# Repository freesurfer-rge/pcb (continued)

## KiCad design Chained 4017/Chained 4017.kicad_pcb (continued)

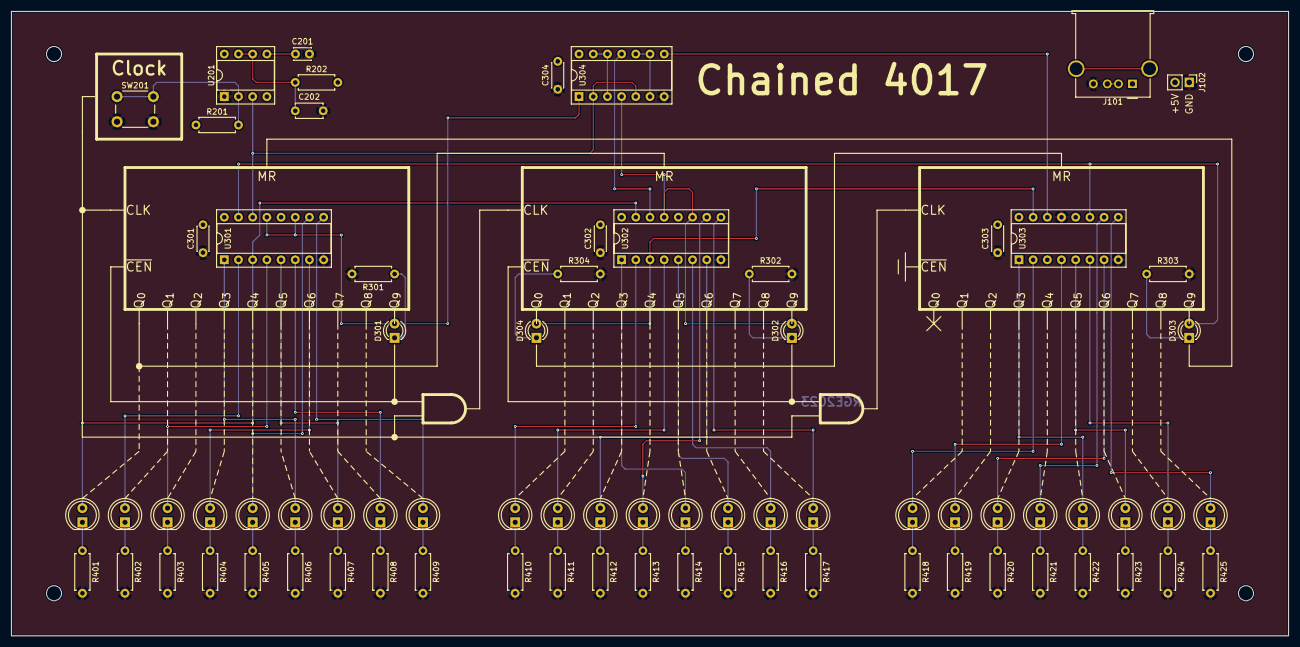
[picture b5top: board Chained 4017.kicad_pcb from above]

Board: 2 copper layers, 228.6 x 111.8 mm, 78 parts (0 on the bottom side), 69 nets.

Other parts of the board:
C301, C302, C303, C304: 0.1u; C_Disc_D4.3mm_W1.9mm_P5.00mm

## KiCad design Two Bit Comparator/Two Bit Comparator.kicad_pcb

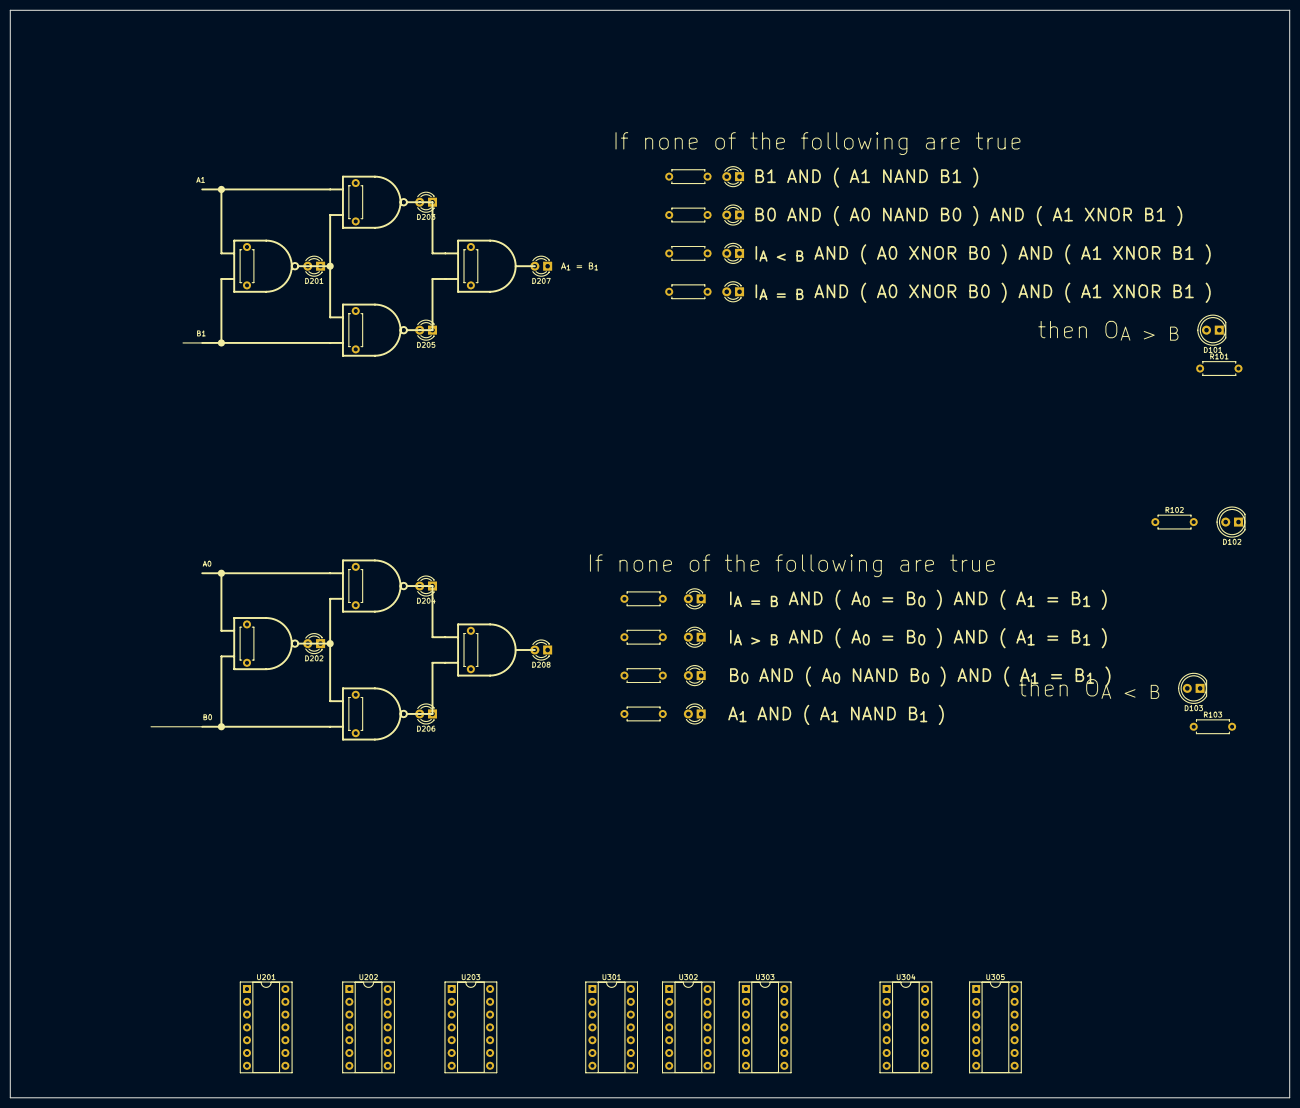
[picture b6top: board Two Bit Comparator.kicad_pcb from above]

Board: 2 copper layers, 254.0 x 215.9 mm, 46 parts (0 on the bottom side), 52 nets, no tracks yet.

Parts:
D101, D102, D103: LED; LED_D5.0mm
D201, D202, D203, D204, D205, D206, D207, D208, D301, D302, D303, D304, D305, D306, D307, D308: LED; LED_D3.0mm
R101, R102, R103, R201, R202, R203, R204, R205, R206, R207, R208, R301, R302, R303, R304, R305, R306, R307, R308: R; R_Axial_DIN0207_L6.3mm_D2.5mm_P7.62mm_Horizontal
U201, U202, U203: 74HC00; DIP-14_W7.62mm_Socket
U301, U302, U303: 74HC10; DIP-14_W7.62mm_Socket
U304, U305: 74HC08; DIP-14_W7.62mm_Socket

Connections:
+5V: U201.14 (VCC), U202.14 (VCC), U203.14 (VCC), U301.5, U301.13, U301.14 (VCC), U302.14 (VCC), U303.14 (VCC), U304.14 (VCC), U305.14 (VCC)
/Accumulate and Output/A0: U201.1, U202.4, U303.11
/Accumulate and Output/A1: U201.4, U202.1, U301.4
/Accumulate and Output/A_{0}NANDB_{0}: R202.1, U201.3, U202.5, U202.9, U302.2, U303.10
/Accumulate and Output/A_{0}XNORB_{0}: R208.1, U203.8, U302.4, U302.10, U303.2, U303.5, U305.12
/Accumulate and Output/A_{1}NANDB_{1}: R201.1, U201.6, U202.2, U202.12, U301.2, U301.3
/Accumulate and Output/A_{1}XNORB_{1}: R207.1, U203.11, U302.3, U302.9, U302.13, U303.1, U303.4, U303.9, U305.13
/Accumulate and Output/B0: U201.2, U202.10, U302.1
/Accumulate and Output/B1: U201.5, U202.13, U301.1
/Accumulate and Output/I_{A=B}: U302.11, U303.13, U304.13
/Accumulate and Output/O_{A<B}: R103.1, U305.8
/Accumulate and Output/O_{A=B}: R102.1, U304.11
/Accumulate and Output/O_{A>B}: R101.1, U304.8
/Accumulate and Output/c0: R301.1, U301.12, U304.1
/Accumulate and Output/c1: R302.1, U302.12, U304.2
/Accumulate and Output/c2: R303.1, U302.6, U304.4
/Accumulate and Output/c3: R304.1, U302.8, U304.5
/Accumulate and Output/c4: R305.1, U303.12, U305.1
/Accumulate and Output/c5: R306.1, U303.6, U305.2
/Accumulate and Output/c6: R307.1, U303.8, U305.4
/Accumulate and Output/c7: R308.1, U301.6, U305.5
/Compare/Ind0: R203.1, U202.3, U203.1
/Compare/Ind1: R205.1, U202.11, U203.2
/Compare/Ind3: R204.1, U202.6, U203.4
/Compare/Ind4: R206.1, U202.8, U203.5
GND: D101.1 (K), D102.1 (K), D103.1 (K), D201.1 (K), D202.1 (K), D203.1 (K), D204.1 (K), D205.1 (K), D206.1 (K), D207.1 (K), D208.1 (K), D301.1 (K), D302.1 (K), D303.1 (K), D304.1 (K), D305.1 (K), D306.1 (K), D307.1 (K), D308.1 (K), U201.7 (GND), U201.9, U201.10, U201.12, U201.13, U202.7 (GND), U203.7 (GND), U301.7 (GND), U301.9, U301.10, U301.11, U302.7 (GND), U303.7 (GND), U304.7 (GND), U305.7 (GND)
unnamed: D101.2 (A), R101.2
unnamed: D102.2 (A), R102.2
unnamed: D103.2 (A), R103.2
unnamed: D201.2 (A), R201.2
unnamed: D202.2 (A), R202.2
unnamed: D203.2 (A), R203.2
unnamed: D204.2 (A), R204.2
unnamed: D205.2 (A), R205.2
unnamed: D206.2 (A), R206.2
unnamed: D207.2 (A), R207.2
unnamed: D208.2 (A), R208.2
unnamed: D301.2 (A), R301.2
unnamed: D302.2 (A), R302.2
unnamed: D303.2 (A), R303.2
unnamed: D304.2 (A), R304.2
unnamed: D305.2 (A), R305.2
unnamed: D306.2 (A), R306.2
unnamed: D307.2 (A), R307.2
unnamed: D308.2 (A), R308.2
unnamed: U203.6, U203.9, U203.10
unnamed: U203.3, U203.12, U203.13
unnamed: U304.3, U304.9
unnamed: U304.6, U304.10
unnamed: U304.12, U305.11
unnamed: U305.3, U305.9
unnamed: U305.6, U305.10

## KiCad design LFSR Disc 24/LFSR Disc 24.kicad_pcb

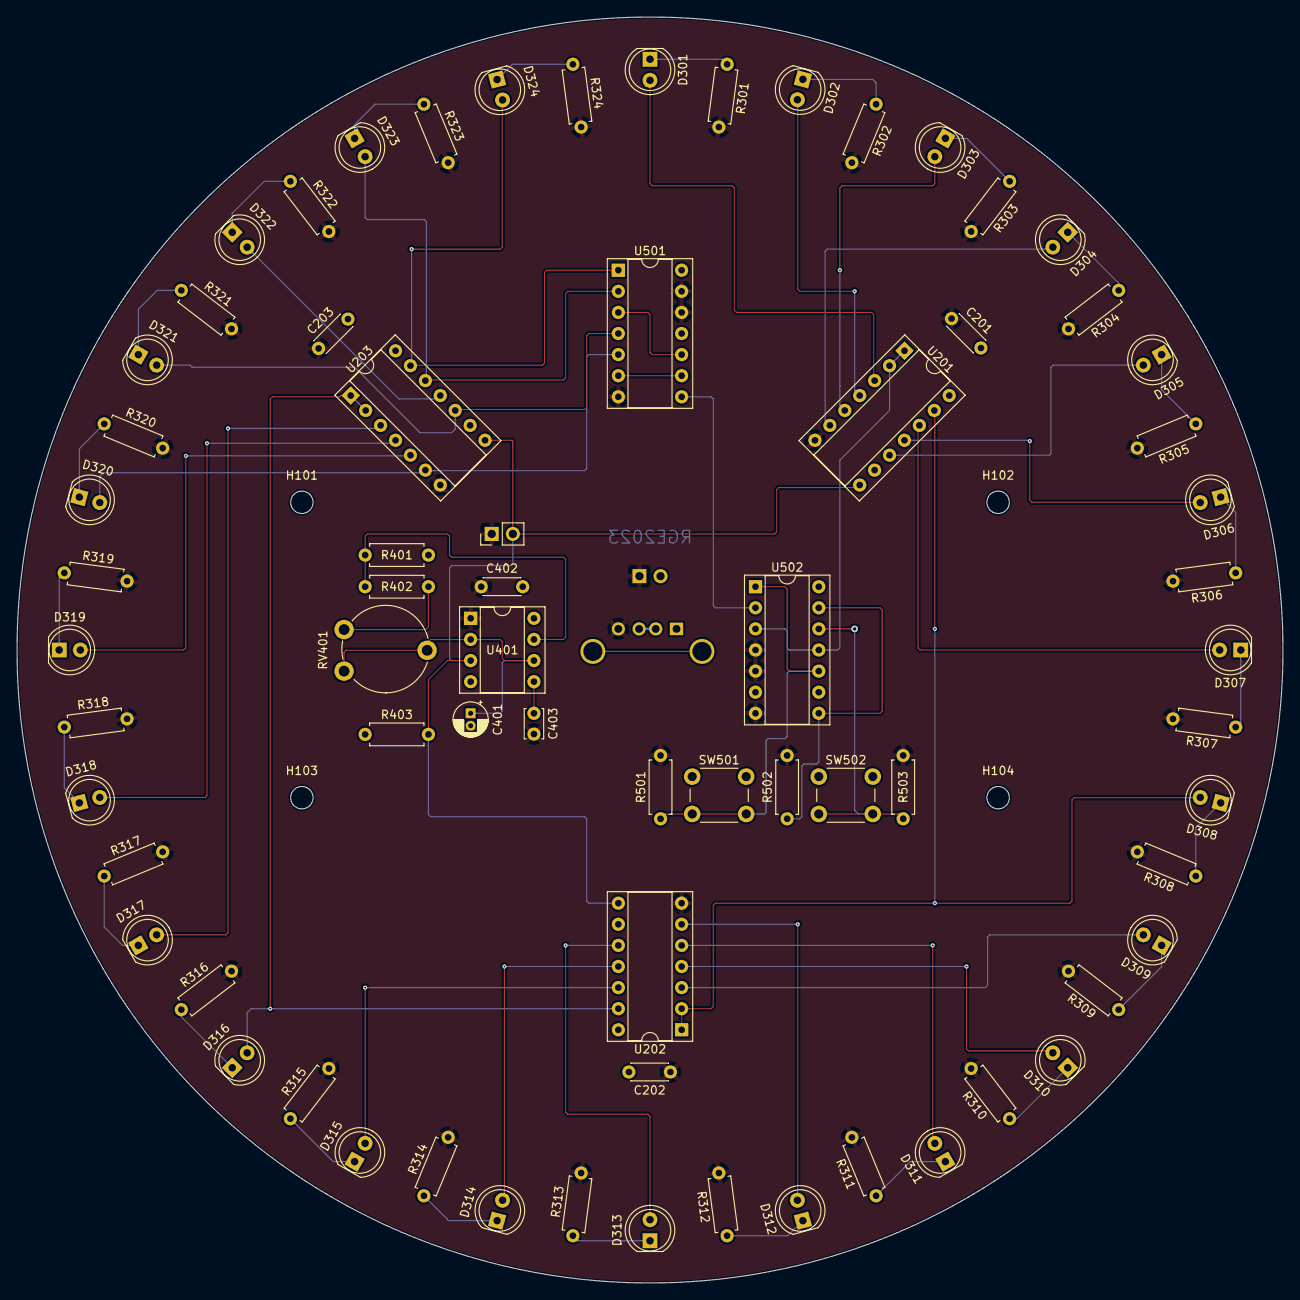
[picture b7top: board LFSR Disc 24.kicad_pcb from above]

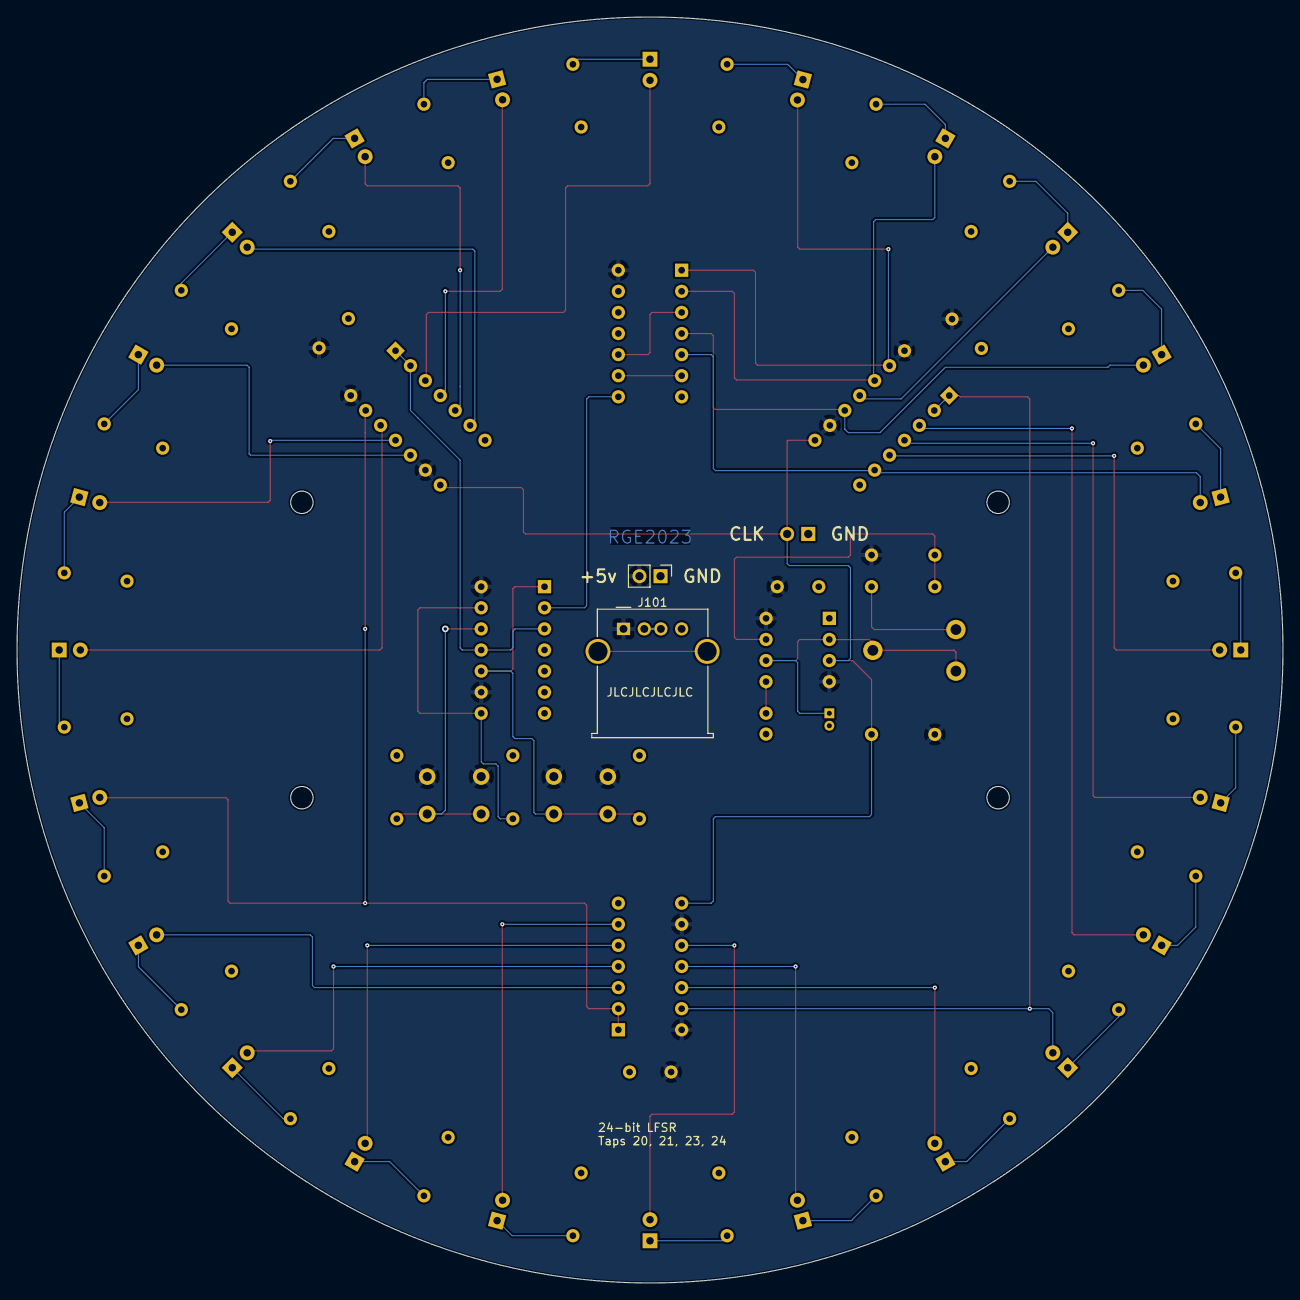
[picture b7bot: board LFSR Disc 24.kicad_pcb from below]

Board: 2 copper layers, 152.4 x 152.4 mm, 76 parts (2 on the bottom side), 63 nets.

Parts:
C201, C202, C203, C402: 0.1u; C_Disc_D4.3mm_W1.9mm_P5.00mm
C401: 10u; CP_Radial_D4.0mm_P1.50mm
C403: 0.01u; C_Disc_D3.4mm_W2.1mm_P2.50mm
D301, D302, D303, D304, D305, D306, D307, D308, D309, D310, D311, D312, D313, D314, D315, D316, D317, D318, D319, D320, D321, D322, D323, D324: LED; LED_D5.0mm
H101, H102, H103, H104: MountingHole; MountingHole_2.7mm_M2.5_ISO7380
J101: USB_A; USB_A_Molex_67643_Horizontal
J102, J401: Conn_01x02_Pin; PinHeader_1x02_P2.54mm_Vertical
R301, R302, R303, R304, R305, R306, R307, R308, R309, R310, R311, R312, R313, R314, R315, R316, R317, R318, R319, R320, R321, R322, R323, R324: 4k7; R_Axial_DIN0207_L6.3mm_D2.5mm_P7.62mm_Horizontal
R401: 10k; R_Axial_DIN0207_L6.3mm_D2.5mm_P7.62mm_Horizontal
R402: 2k2; R_Axial_DIN0207_L6.3mm_D2.5mm_P7.62mm_Horizontal
R403: 1k; R_Axial_DIN0207_L6.3mm_D2.5mm_P7.62mm_Horizontal
R501, R502, R503: 100k; R_Axial_DIN0207_L6.3mm_D2.5mm_P7.62mm_Horizontal
RV401: 100k; Potentiometer_Piher_PT-10-V10_Vertical
SW501, SW502: SW_SPST; SW_PUSH_6mm
U201, U202, U203: 74HC164; DIP-14_W7.62mm_Socket
U401: LM555xN; DIP-8_W7.62mm_Socket
U501: 74HC86; DIP-14_W7.62mm_Socket
U502: 74HCT125; DIP-14_W7.62mm_Socket

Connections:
+5V: C201.2, C202.2, C203.2, C402.2, J101.1 (VBUS), J102.2, R401.2, R403.1, SW501.1 (A), SW502.1 (A), U201.9 (~MR), U201.14 (VCC), U202.9 (~MR), U202.14 (VCC), U203.9 (~MR), U203.14 (VCC), U401.4 (R), U401.8 (VCC), U501.14 (VCC), U502.9, U502.14 (VCC)
/LED Output/LED1: D301.2 (A), U201.3 (Q0)
/LED Output/LED2: D302.2 (A), U201.4 (Q1)
/LED Output/LED3: D303.2 (A), U201.5 (Q2)
/LED Output/LED4: D304.2 (A), U201.6 (Q3)
/LED Output/LED5: D305.2 (A), U201.10 (Q4)
/LED Output/LED6: D306.2 (A), U201.11 (Q5)
/LED Output/LED7: D307.2 (A), U201.12 (Q6)
/LED Output/LED8: D308.2 (A), U201.13 (Q7), U202.1 (DSA), U202.2 (DSB)
/LED Output/LED9: D309.2 (A), U202.3 (Q0)
/LED Output/LED10: D310.2 (A), U202.4 (Q1)
/LED Output/LED11: D311.2 (A), U202.5 (Q2)
/LED Output/LED12: D312.2 (A), U202.6 (Q3)
/LED Output/LED13: D313.2 (A), U202.10 (Q4)
/LED Output/LED14: D314.2 (A), U202.11 (Q5)
/LED Output/LED15: D315.2 (A), U202.12 (Q6)
/LED Output/LED16: D316.2 (A), U202.13 (Q7), U203.1 (DSA), U203.2 (DSB)
/LED Output/LED17: D317.2 (A), U203.3 (Q0)
/LED Output/LED18: D318.2 (A), U203.4 (Q1)
/LED Output/LED19: D319.2 (A), U203.5 (Q2)
/LED Output/LED20: D320.2 (A), U203.6 (Q3), U501.5
/LED Output/LED21: D321.2 (A), U203.10 (Q4), U501.4
/LED Output/LED22: D322.2 (A), U203.11 (Q5)
/LED Output/LED23: D323.2 (A), U203.12 (Q6), U501.2
/LED Output/LED24: D324.2 (A), U203.13 (Q7), U501.1
/Shift Clock/CLK: J401.2, R403.2, U201.8 (CP), U202.8 (CP), U203.8 (CP), U401.3 (Q)
/Shift Clock/DIVIDER: R401.1, R402.1, U401.7 (DIS)
/Shift Clock/TRTHR: C401.1, RV401.1, RV401.2, U401.2 (TR), U401.6 (THR)
/Shift Registers/Feedback/NXTBIT: U201.1 (DSA), U201.2 (DSB), U502.3, U502.11
/Shift Registers/Feedback/~FEEDBACK: R501.1, SW501.2 (B), U502.1, U502.10
/Shift Registers/Feedback/~MANUAL: R502.1, U502.8, U502.13
GND: C201.1, C202.1, C203.1, C401.2, C402.1, C403.2, J101.4 (GND), J102.1, J401.1, R301.2, R302.2, R303.2, R304.2, R305.2, R306.2, R307.2, R308.2, R309.2, R310.2, R311.2, R312.2, R313.2, R314.2, R315.2, R316.2, R317.2, R318.2, R319.2, R320.2, R321.2, R322.2, R323.2, R324.2, R501.2, R502.2, R503.2, U201.7 (GND), U202.7 (GND), U203.7 (GND), U401.1 (GND), U501.7 (GND), U501.12, U501.13, U502.4, U502.5, U502.7 (GND)
unnamed: D301.1 (K), R301.1
unnamed: D302.1 (K), R302.1
unnamed: D303.1 (K), R303.1
unnamed: D304.1 (K), R304.1
unnamed: D305.1 (K), R305.1
unnamed: D306.1 (K), R306.1
unnamed: D307.1 (K), R307.1
unnamed: D308.1 (K), R308.1
unnamed: D309.1 (K), R309.1
unnamed: D310.1 (K), R310.1
unnamed: D311.1 (K), R311.1
unnamed: D312.1 (K), R312.1
unnamed: D313.1 (K), R313.1
unnamed: D314.1 (K), R314.1
unnamed: D315.1 (K), R315.1
unnamed: D316.1 (K), R316.1
unnamed: D317.1 (K), R317.1
unnamed: D318.1 (K), R318.1
unnamed: D319.1 (K), R319.1
unnamed: D320.1 (K), R320.1
unnamed: D321.1 (K), R321.1
unnamed: D322.1 (K), R322.1
unnamed: D323.1 (K), R323.1
unnamed: D324.1 (K), R324.1
unnamed: J101.2 (D-), J101.3 (D+)
unnamed: R402.2, RV401.3
unnamed: R503.1, SW502.2 (B), U502.12
unnamed: C403.1, U401.5 (CV)
unnamed: U501.6, U501.9
unnamed: U501.8, U502.2
unnamed: U501.3, U501.10

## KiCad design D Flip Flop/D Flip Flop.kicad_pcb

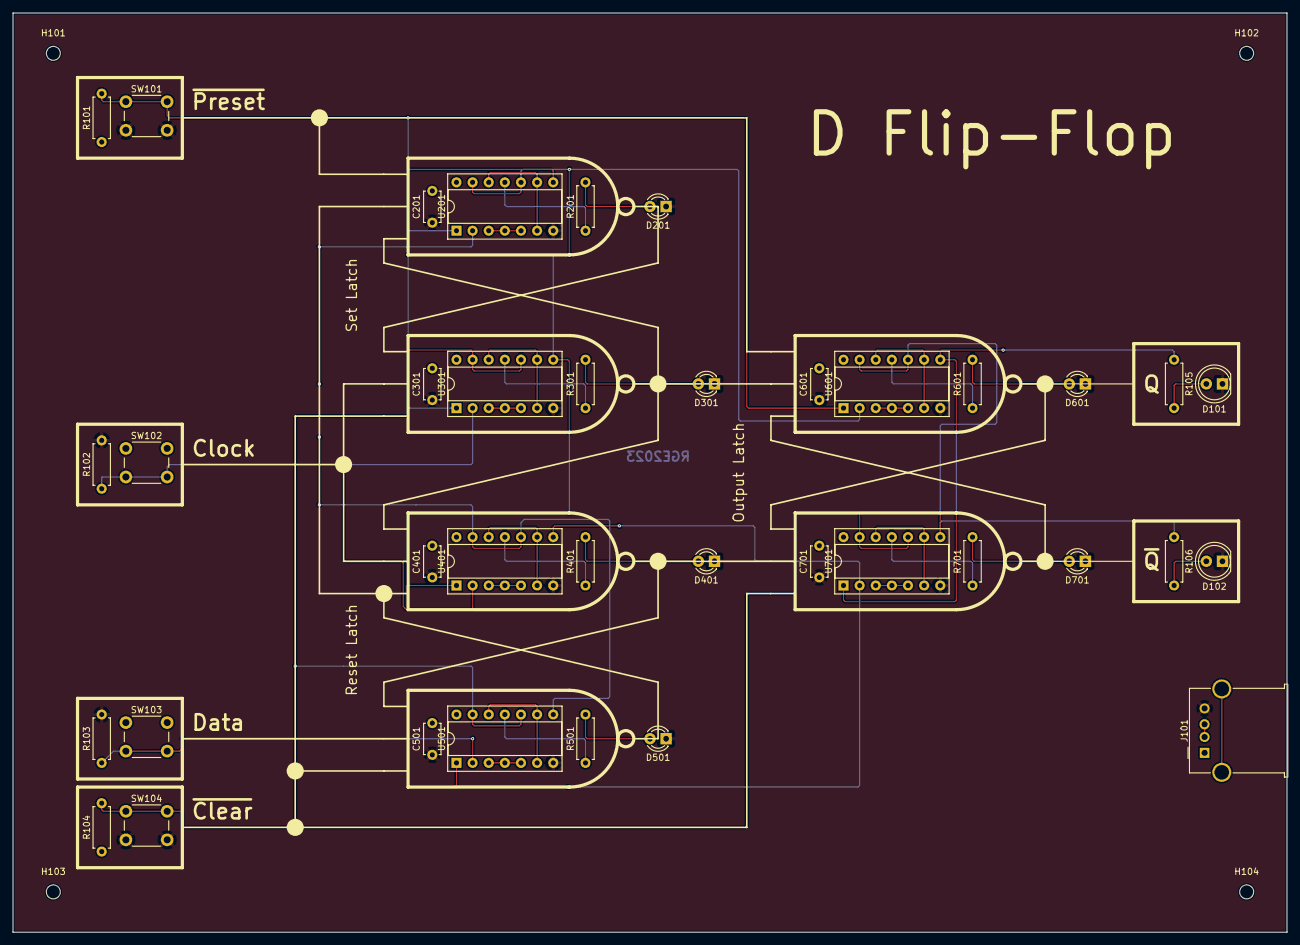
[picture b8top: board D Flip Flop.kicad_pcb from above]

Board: 2 copper layers, 200.7 x 144.8 mm, 41 parts (0 on the bottom side), 39 nets.

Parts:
C201, C301, C401, C501, C601, C701: 100n; C_Disc_D4.7mm_W2.5mm_P5.00mm
D101, D102: LED; LED_D5.0mm
D201, D301, D401, D501, D601, D701: LED; LED_D3.0mm
H101, H102, H103, H104: MountingHole; MountingHole_2.2mm_M2
J101: USB_A; USB_A_Molex_67643_Horizontal
R101, R102, R103, R104: 100k; R_Axial_DIN0207_L6.3mm_D2.5mm_P7.62mm_Horizontal
R105, R106, R201, R301, R401, R501, R601, R701: 4k7; R_Axial_DIN0207_L6.3mm_D2.5mm_P7.62mm_Horizontal
SW101, SW102, SW103, SW104: SW_Push; SW_PUSH_6mm_H4.3mm
U201, U301, U401, U501, U601, U701: 74HC00; DIP-14_W7.62mm_Socket

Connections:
+5V: C201.2, C301.2, C401.2, C501.2, C601.2, C701.2, J101.1 (VBUS), R101.1, R104.1, SW102.1, SW103.1, U201.14 (VCC), U301.14 (VCC), U401.14 (VCC), U501.14 (VCC), U601.14 (VCC), U701.14 (VCC)
/CLK: R102.1, SW102.2, U301.2, U401.2
/DATA: R103.1, SW103.2, U501.2
/NAND 0/B: U201.2, U401.10, U401.13, U501.8
/NAND 0/C: U201.10, U201.13, U301.8, U401.1, U601.2
/NAND 0/OUT: U201.8, U301.1
/NAND 2/OUT: U401.8, U501.1, U701.2
/Q: R105.1, U601.8, U701.1
/~CLEAR: R104.2, SW104.1, U301.10, U301.13, U501.10, U501.13, U701.10, U701.13
/~PRESET: R101.2, SW101.1, U201.1, U601.1
/~Q: R106.1, U601.10, U601.13, U701.8
GND: C201.1, C301.1, C401.1, C501.1, C601.1, C701.1, D101.1 (K), D102.1 (K), D201.1 (K), D301.1 (K), D401.1 (K), D501.1 (K), D601.1 (K), D701.1 (K), J101.4 (GND), R102.2, R103.2, SW101.2, SW104.2, U201.7 (GND), U301.7 (GND), U401.7 (GND), U501.7 (GND), U601.7 (GND), U701.7 (GND)
unnamed: D101.2 (A), R105.2
unnamed: D102.2 (A), R106.2
unnamed: D201.2 (A), R201.2
unnamed: D301.2 (A), R301.2
unnamed: D401.2 (A), R401.2
unnamed: D501.2 (A), R501.2
unnamed: D601.2 (A), R601.2
unnamed: D701.2 (A), R701.2
unnamed: J101.2 (D-), J101.3 (D+)
unnamed: R201.1, U201.11
unnamed: R301.1, U301.11
unnamed: R401.1, U401.11
unnamed: R501.1, U501.11
unnamed: R601.1, U601.11
unnamed: R701.1, U701.11
unnamed: U201.3, U201.4, U201.5
unnamed: U201.6, U201.9, U201.12
unnamed: U301.3, U301.4, U301.5
unnamed: U301.6, U301.9, U301.12
unnamed: U401.3, U401.4, U401.5
unnamed: U401.6, U401.9, U401.12
unnamed: U501.3, U501.4, U501.5
unnamed: U501.6, U501.9, U501.12
unnamed: U601.3, U601.4, U601.5
unnamed: U601.6, U601.9, U601.12
unnamed: U701.3, U701.4, U701.5
unnamed: U701.6, U701.9, U701.12

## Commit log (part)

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2021-03-20 Putting in the first project
2021-03-20 Move over the 8x8 LED Array
2021-03-20 Adding the Linear Feedback Shift Register project
2021-03-21 Ignore gerber generation
2021-03-21 And ignore the zipped file
2021-03-21 Add location for order number
2021-03-30 Had address register connected backwards on LED 8x8
2021-04-07 Fix capacitor
2021-04-18 Adding a circuit for macro 555 chip
2021-04-19 Trying a current sensor
2021-06-16 Starting out
2021-06-16 Adding in clocks
2021-06-16 Working through basics of the LFSR
2021-06-16 Add power-on reset
2021-06-18 Routing the registers
2021-06-19 Working on letters
2021-06-19 Really add the letters
2021-06-19 Fix output enable, and do some routing
2021-06-19 Fiddling update
2021-06-20 Add fabrication number and Coppermark
2021-06-28 Add SMD Emma badge (#1)
    Initial version of an SMD linear feedback shift register, connected to 'EMMA' in LEDs.
2021-09-05 Adding files
2021-09-05 SPI LED Display (#2)
    Adding the SPI-driven 8x8 LED display
2021-09-05 Working on comparator
2021-09-05 Reorganising
2021-09-05 Starting rough routing
2021-09-05 More routing.... not very happy
2021-09-06 Rerouting everything
2021-09-06 Preliminary routing
2021-09-06 Add mounting holes
2021-09-07 PWM Channel v1 (#3)
    First attempt at creating a PWM Channel, using a counter and digital comparators.
2021-09-11 Basic Circuit
2021-09-11 Change to PNP
2021-09-11 Adding footprint and initial routing
2021-09-11 Routing
2021-09-11 Make sure of save
2021-09-26 Transistor Astable (#4)
    First pass at a pair of blinking transistors
2021-09-26 Tweak to PWM
2021-09-26 Updating values
2021-09-26 More values
2021-09-26 Filling in resistors
2021-09-26 Missed some
2021-09-26 Four more
2021-09-26 Values for 8x8 LED Display (#5)
    Some part values were missed on the SPI-driven LED matrix. Remedy this.
2021-10-09 Moving to 8-bit and adding indicator LEDs
2021-10-09 Make sure everything is in order
2021-10-09 Rerouting and adding LEDs
2021-10-10 Change LED resistors to 4k7
2021-10-10 Forgot one
2021-10-16 Change capacitor
2021-10-17 Review before production
2021-10-17 Updates to PWM Channel Board (#6)
    Add a number of LED indicators and reduce from 12-bit to 8-bit
2021-11-20 Formulating
2021-11-20 Finishing design
2021-11-20 Correct IC name
2021-11-20 Add 3V3 to 5V output level shifter (#7)
    A level shifter to convert 3V3 outputs (such as those on the Pi) to 5V ones.
2021-11-20 Experimenting.... adding new schema symbol
2021-11-20 Working on things...
2021-11-21 Finishing draft
2021-11-21 Pico Interface for 32x32 LED Array (#8)
    Simple board to interface a Raspberry Pi Pico (via headers) to a 32x32 RGB LED Array. Includes required level shifter ICs. This is [based on the Adafruit tutorial](https://learn.adafruit.com/32x16-32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
2021-11-21 Fixing TSSOP footprints
2021-11-26 Fixing TSSOP footprints (#9)
    Fixes the footprints of the TSSOP packages, after JLCPCB caught the error.
    Since order, I've noticed two more issues:
    - The decoupling capacitors may need larger footprints too (there was a warning about them, but JLCPCB didn't message me like they did for the TSSOP footprints)
    - The pinout from the Pico needs to change. I've been learning about the differences between `out`, `set` and `sideset` pins since the order went into production
2021-11-26 Initial commit, still routing
2021-11-26 Some adjustments
2021-11-26 Final tweaks
2021-11-26 Shift register tutorial (#10)
    A simple tutorial board for the 74164 SIPO shift register.
2021-12-11 Disconnect indicator LEDs
2021-12-11 Rerouting board
2021-12-12 Make gerbers
2021-12-12 Working on reordering connections
2021-12-12 Some more routine
2021-12-12 Fix shift register tutorial (#11)
    I had forgotten how NPN transistors worked, which resulted in the push buttons not affecting their target pins. Remove the transistors & indicator LEDs, and shrink the board.
2021-12-12 Thinking a little about power
2021-12-12 Rethinking sideset pins slightly
2021-12-25 Removing old things
2021-12-25 Working circuit together
2021-12-25 Ordered design
2021-12-25 Another attempt at the Shift Registers (#12)
    It appears that clock pins are very finicky about debouncing. Switch to using a 555 monostable for this purpose, and remove debounce from the other pins. The 'data' pin only matters on the clock edge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
2022-11-04 Getting started
2022-11-04 Don't track KiCad's backup files
2022-11-06 Working on input stage
2022-11-06 Working on decoder stage
2022-11-07 Go with individual chips for AND gates
2022-11-08 Rethinking NOT gates and starting on output
2022-11-09 Finish roughing out board
2022-11-10 Working on routing
2022-11-11 Fixing vias
2022-11-11 Getting ready for production
2022-11-24 First pass at a tiny SMD
2022-11-24 Preparing for production
2022-11-24 Astable Transitor SMD project (#13)
    Want to try out SMD assembly with KiCad 6
2022-12-03 Demultiplexer (#14)
    A 1-to-4 demultiplexer implemented using gates.
2022-12-03 Starting on counter
2022-12-03 Adding the clock push button
2022-12-03 Getting flipflop board locations worked out
2022-12-04 Routing...
2022-12-04 Finishing routing, silkscreen and mounting
2022-12-04 Forgot to add order locator
2022-12-04 Add Johnson counter with decoder (#15)
    A four stage counter, with a decoder for eight sequential LEDs.
2022-12-31 Working on assembly
2022-12-31 Rough layout
2022-12-31 Completed first draft
2022-12-31 Don't need monostable for clock
2023-01-01 Simplifying board a little
2023-01-01 Clean up ERC warnings
2023-01-01 Final refill for production
2023-01-01 Add D Flip-Flop (#16)
    Adding a D Flip-Flop based on four NAND gates.
2023-09-10 Starting work
2023-09-10 Filling things out a little
2023-09-11 More things assembling
2023-09-11 Board layout and schematic tweaks
2023-09-13 Final routing
2023-09-14 Update some values
2023-09-14 Holes, silkscreen....
2023-09-14 LFSR Disc (#17)
    A 24-bit linear feedback shift register, arranged on a disc.
2023-10-15 Starting on accumulation/output stage
2023-10-15 Thinking about the layout
2023-10-21 Starting the board
2023-10-21 Working through things
2023-10-21 Zone fills
2023-10-25 Starting design
2023-10-25 Routing quickly
2023-10-28 Starting schematic
2023-10-29 Roughing out PCB layout
2023-10-29 More layout
2023-10-29 Layout and starting routing
2023-10-29 Capacitors and routing
2023-10-29 Complete routing
2023-10-29 Minor correction
2023-10-29 Sending for fabrication
2023-10-29 Three boards (#18)
    Three new boards:
    - Running 4017 counter
    - Binary Counter with flip-flops
    - Chain of three 4017s
2024-10-20 Initial test
2024-10-20 Update for production
2024-10-20 Edge Connector (#19)
    A simple board to iterate on the TE-5530843-4 connector. This is an edge connector, so there are two footprints: the actual connector and the corresponding board edge.
